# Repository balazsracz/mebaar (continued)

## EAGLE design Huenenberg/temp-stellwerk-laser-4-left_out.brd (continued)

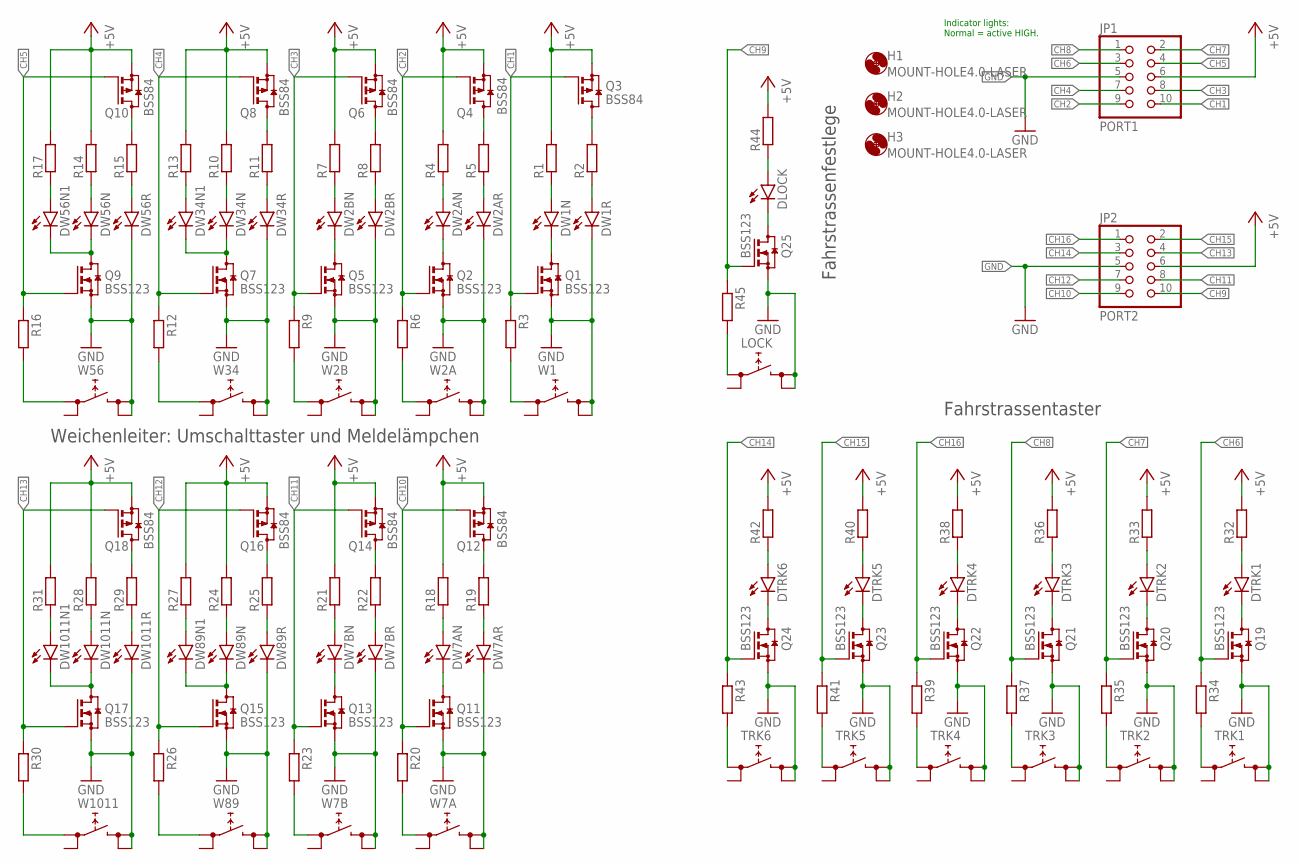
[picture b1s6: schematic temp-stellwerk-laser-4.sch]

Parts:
DLOCK: LEDCHIPLED_0805; CHIPLED_0805
DTRK1, DTRK2, DTRK3, DTRK4, DTRK5, DTRK6: LEDCHIPLED_0805; CHIPLED_0805
DW1N, DW1R, DW2AN, DW2AR, DW7AN, DW7AR: LEDCHIPLED_0603; CHIPLED_0603
DW2BN, DW2BR, DW7BN, DW7BR, DW34N, DW34N1, DW34R, DW56N, DW56N1, DW56R, DW89N, DW89N1, DW89R, DW1011N, DW1011N1, DW1011R: LEDCHIPLED_0805; CHIPLED_0805
H1, H2, H3: MOUNT-HOLE4.0-LASER; MOUNT-HOLE-3.2-4.0-LASER
JP1: PORT1; CON10M
JP2: PORT2; CON10M
LOCK: LOCK; TACTSW-6X6-LASER
Q1, Q2, Q5, Q7, Q9, Q11, Q13, Q15, Q17, Q19, Q20, Q21, Q22, Q23, Q24, Q25: BSS123; SOT23-NCH
Q3, Q4, Q6, Q8, Q10, Q12, Q14, Q16, Q18: BSS84; SOT23
R1, R2, R3, R4, R5, R6, R7, R8, R9, R10, R11, R12, R13, R14, R15, R16, R17, R18, R19, R20, R21, R22, R23, R24, R25, R26, R27, R28, R29, R30, R31, R32, R33, R34, R35, R36, R37, R38, R39, R40, R41, R42, R43, R44, R45: R-EU_R0805; R0805
TRK1, TRK2, TRK3, TRK4, TRK5, TRK6: TACTSW-6X6S; TACTSW-6X6-LASER
W1: W1; TACTSW-6X6-LASER
W2A, W2B, W7A, W7B: TACTSW-6X6S; TACTSW-6X6-LASER
W34, W56, W89, W1011: XOVER; TACTSW-6X6-LASER

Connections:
+5V: JP1.6, JP2.6, Q3.2 (S), Q4.2 (S), Q6.2 (S), Q8.2 (S), Q10.2 (S), Q12.2 (S), Q14.2 (S), Q16.2 (S), Q18.2 (S), R1.2, R4.2, R7.2, R10.2, R13.2, R14.2, R17.2, R18.2, R21.2, R24.2, R27.2, R28.2, R31.2, R32.2, R33.2, R36.2, R38.2, R40.2, R42.2, R44.2
CH1: JP1.10, Q1.1 (G), Q3.1 (G), R3.1
CH2: JP1.9, Q2.1 (G), Q4.1 (G), R6.1
CH3: JP1.8, Q5.1 (G), Q6.1 (G), R9.1
CH4: JP1.7, Q7.1 (G), Q8.1 (G), R12.1
CH5: JP1.4, Q9.1 (G), Q10.1 (G), R16.1
CH6: JP1.3, Q19.1 (G), R34.1
CH7: JP1.2, Q20.1 (G), R35.1
CH8: JP1.1, Q21.1 (G), R37.1
CH9: JP2.10, Q25.1 (G), R45.1
CH10: JP2.9, Q11.1 (G), Q12.1 (G), R20.1
CH11: JP2.8, Q13.1 (G), Q14.1 (G), R23.1
CH12: JP2.7, Q15.1 (G), Q16.1 (G), R26.1
CH13: JP2.4, Q17.1 (G), Q18.1 (G), R30.1
CH14: JP2.3, Q24.1 (G), R43.1
CH15: JP2.2, Q23.1 (G), R41.1
CH16: JP2.1, Q22.1 (G), R39.1
GND: DW1R.C, DW2AR.C, DW2BR.C, DW7AR.C, DW7BR.C, DW34R.C, DW56R.C, DW89R.C, DW1011R.C, JP1.5, JP2.5, LOCK.3 (2.1), LOCK.4 (2.2), Q1.2 (S), Q2.2 (S), Q5.2 (S), Q7.2 (S), Q9.2 (S), Q11.2 (S), Q13.2 (S), Q15.2 (S), Q17.2 (S), Q19.2 (S), Q20.2 (S), Q21.2 (S), Q22.2 (S), Q23.2 (S), Q24.2 (S), Q25.2 (S), TRK1.3 (2.1), TRK1.4 (2.2), TRK2.3 (2.1), TRK2.4 (2.2), TRK3.3 (2.1), TRK3.4 (2.2), TRK4.3 (2.1), TRK4.4 (2.2), TRK5.3 (2.1), TRK5.4 (2.2), TRK6.3 (2.1), TRK6.4 (2.2), W1.3 (2.1), W1.4 (2.2), W2A.3 (2.1), W2A.4 (2.2), W2B.3 (2.1), W2B.4 (2.2), W7A.3 (2.1), W7A.4 (2.2), W7B.3 (2.1), W7B.4 (2.2), W34.3 (2.1), W34.4 (2.2), W56.3 (2.1), W56.4 (2.2), W89.3 (2.1), W89.4 (2.2), W1011.3 (2.1), W1011.4 (2.2)
unnamed: DTRK1.C, Q19.3 (D)
unnamed: DW1N.C, Q1.3 (D)
unnamed: DW1N.A, R1.1
unnamed: DW1R.A, R2.1
unnamed: Q3.3 (D), R2.2
unnamed: DW2AN.C, Q2.3 (D)
unnamed: R3.2, W1.1 (1.1)
unnamed: DW2AN.A, R4.1
unnamed: DW2AR.A, R5.1
unnamed: Q4.3 (D), R5.2
unnamed: R6.2, W2A.1 (1.1)
unnamed: DW2BN.C, Q5.3 (D)
unnamed: DW2BN.A, R7.1
unnamed: DW2BR.A, R8.1
unnamed: Q6.3 (D), R8.2
unnamed: R9.2, W2B.1 (1.1)
unnamed: DW56N.A, R14.1
unnamed: DW34N.A, R10.1
unnamed: DW34R.A, R11.1
unnamed: Q8.3 (D), R11.2
unnamed: R12.2, W34.1 (1.1)
unnamed: DW34N.C, DW34N1.C, Q7.3 (D)
unnamed: DW34N1.A, R13.1
unnamed: DW56R.A, R15.1
unnamed: Q10.3 (D), R15.2
unnamed: R16.2, W56.1 (1.1)
unnamed: DW56N.C, DW56N1.C, Q9.3 (D)
unnamed: DW56N1.A, R17.1
unnamed: DW7AN.C, Q11.3 (D)
unnamed: DW7AN.A, R18.1
unnamed: DW7AR.A, R19.1
unnamed: Q12.3 (D), R19.2
unnamed: R20.2, W7A.1 (1.1)
unnamed: DW7BN.C, Q13.3 (D)
unnamed: DW7BN.A, R21.1
unnamed: DW7BR.A, R22.1
unnamed: Q14.3 (D), R22.2
unnamed: R23.2, W7B.1 (1.1)
unnamed: DW89N.A, R24.1
unnamed: DW89R.A, R25.1
unnamed: Q16.3 (D), R25.2
unnamed: R26.2, W89.1 (1.1)
unnamed: DW89N.C, DW89N1.C, Q15.3 (D)
unnamed: DW89N1.A, R27.1
unnamed: DW1011N.A, R28.1
unnamed: DW1011R.A, R29.1
unnamed: Q18.3 (D), R29.2
unnamed: R30.2, W1011.1 (1.1)
unnamed: DW1011N.C, DW1011N1.C, Q17.3 (D)
unnamed: DW1011N1.A, R31.1
unnamed: DTRK1.A, R32.1
unnamed: DTRK2.C, Q20.3 (D)
unnamed: DTRK2.A, R33.1
unnamed: R34.2, TRK1.1 (1.1)
unnamed: R35.2, TRK2.1 (1.1)
unnamed: DTRK3.C, Q21.3 (D)
unnamed: DTRK3.A, R36.1
unnamed: R37.2, TRK3.1 (1.1)
unnamed: DTRK4.C, Q22.3 (D)
unnamed: DTRK4.A, R38.1
unnamed: R39.2, TRK4.1 (1.1)
unnamed: DTRK5.C, Q23.3 (D)
unnamed: DTRK5.A, R40.1
unnamed: R41.2, TRK5.1 (1.1)
unnamed: DTRK6.C, Q24.3 (D)
unnamed: DTRK6.A, R42.1
unnamed: R43.2, TRK6.1 (1.1)
unnamed: DLOCK.C, Q25.3 (D)
unnamed: DLOCK.A, R44.1
unnamed: LOCK.1 (1.1), R45.2

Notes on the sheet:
Indicator lights: Normal = active HIGH.
Weichenleiter: Umschalttaster und Meldelämpchen
Fahrstrassentaster
Fahrstrassenfestlege

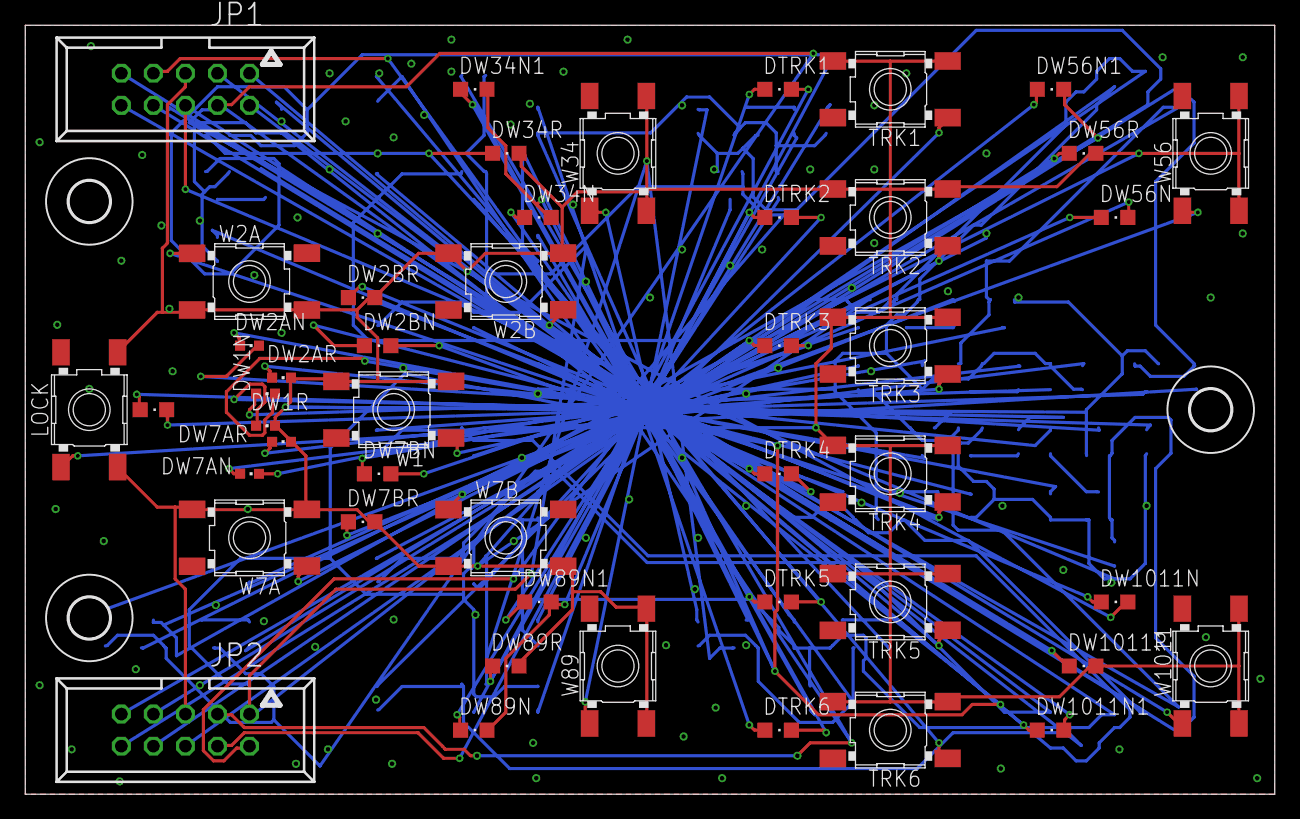
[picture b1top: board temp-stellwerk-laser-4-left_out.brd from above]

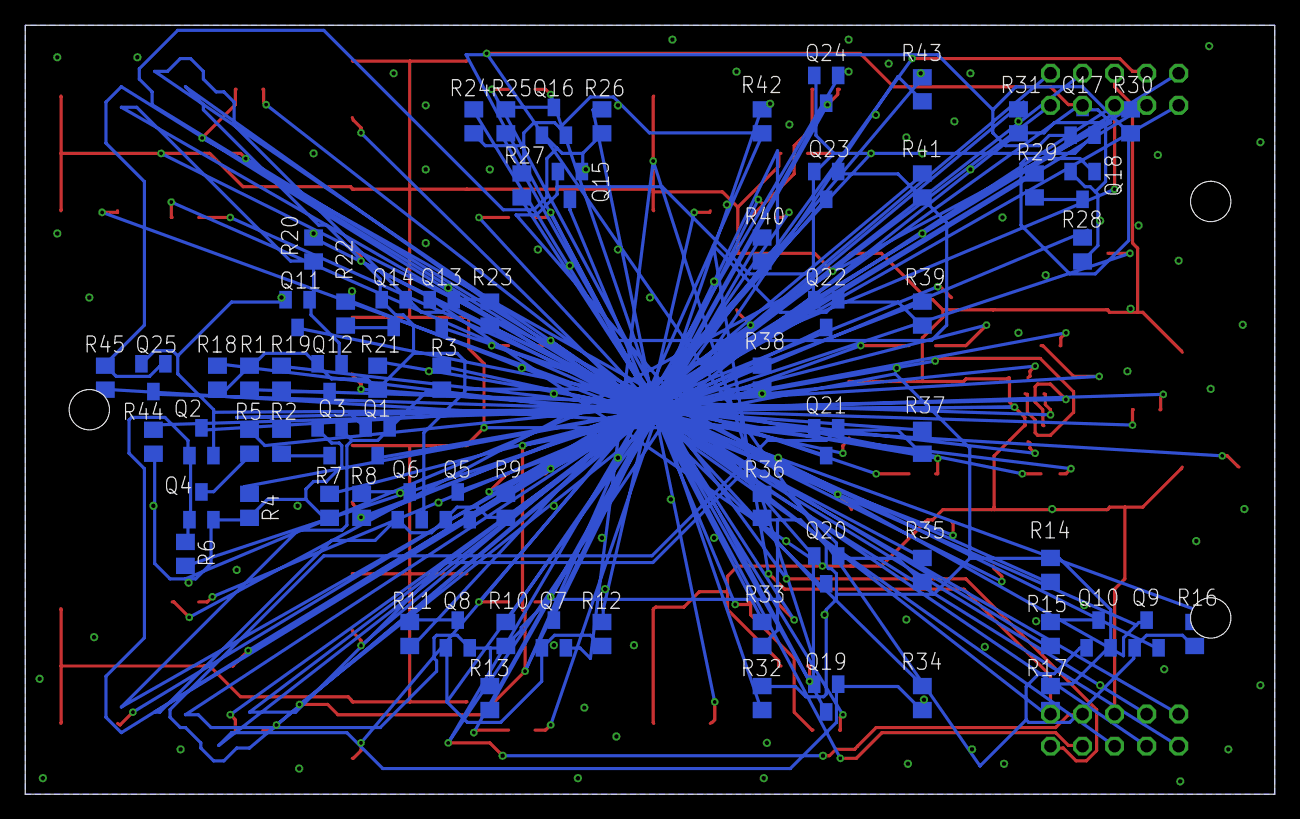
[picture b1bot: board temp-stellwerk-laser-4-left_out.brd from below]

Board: 2 copper layers, 99.1 x 61.0 mm, 138 parts (70 on the bottom side), 88 nets.

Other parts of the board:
PLABEL0: PLABEL0
PLABEL1: PLABEL1
PLABEL2: PLABEL2
PLABEL3: PLABEL3
PLABEL4: PLABEL4
PLABEL5: PLABEL5
PLABEL6: PLABEL6
PLABEL7: PLABEL7
PLABEL8: PLABEL8
PLABEL9: PLABEL9
PLABEL10: PLABEL10
PLABEL11: PLABEL11
PLABEL12: PLABEL12
PLABEL13: PLABEL13
PLABEL14: PLABEL14
PLABEL15: PLABEL15
PLABEL16: PLABEL16
PLABEL17: PLABEL17

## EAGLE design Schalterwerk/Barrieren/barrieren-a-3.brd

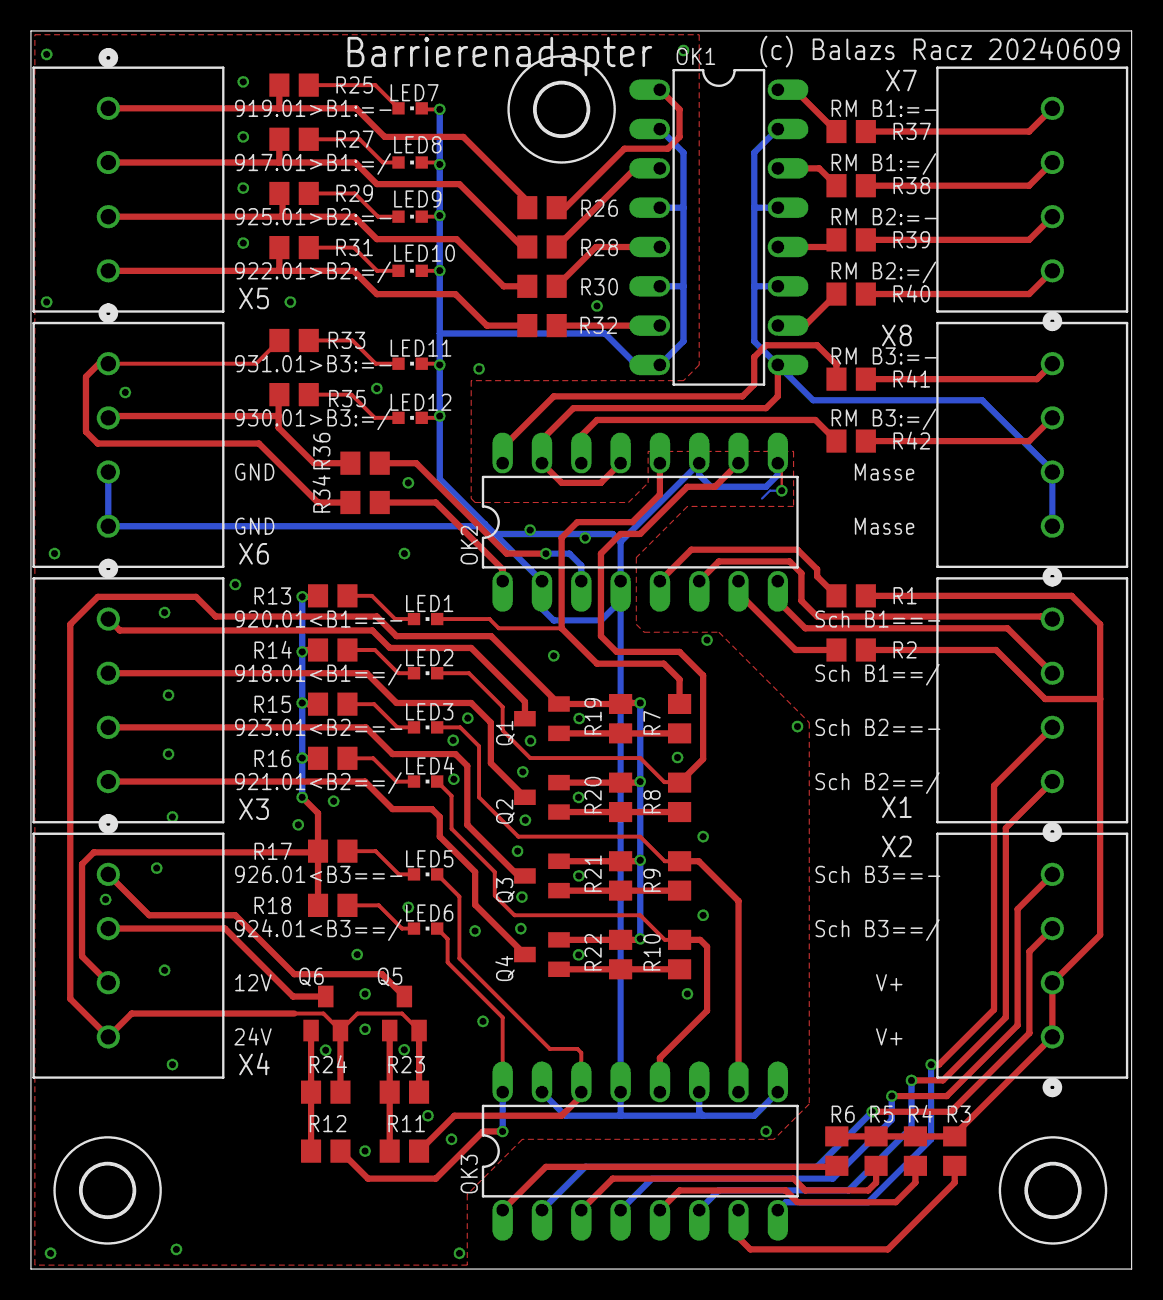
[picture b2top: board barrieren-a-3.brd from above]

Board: 2 copper layers, 71.1 x 80.0 mm, 74 parts (0 on the bottom side), 71 nets.

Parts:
H2, H3, H4: MOUNT-HOLE3.3; 3,3
LED1, LED2, LED3, LED4, LED5, LED6, LED7, LED8, LED9, LED10, LED11, LED12: CHIPLED_0603
OK1, OK2, OK3: PC847; DIL16
Q1, Q2, Q3, Q4, Q5, Q6: BSS84; SOT23-PCH
R1, R2, R3, R4, R5, R6: 1k5; R0805
R7, R8, R9, R10, R11, R12, R19, R20, R21, R22, R23, R24: 100k; R0805
R13, R14, R15, R16, R17, R18: 10k; R0805
R25, R26, R27, R28, R29, R30, R31, R32, R33, R34, R35, R36: 5k; R0805
R37, R38, R39, R40, R41, R42: 100; R0805
X1, X2, X3, X4, X5, X6, X7, X8: PHNX_4P_350CONN_1984989_PXC; PHNX_4P_350

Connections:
+12V: R13.2, R14.2, R15.2, R16.2, R17.2, R18.2, X4.3
+15V: R1.1, R2.1, R3.1, R4.1, R5.1, R6.1, X2.1, X2.2
+24V: Q1.2, Q2.2, Q3.2, Q4.2, Q5.2, Q6.2, R19.2, R20.2, R21.2, R22.2, R23.2, R24.2, X4.4
AGND: OK1.9, OK1.11, OK1.13, OK1.15, OK2.13, OK2.15, X8.1, X8.2
B1-ACT-CL: R25.2, R26.2, X5.1
B1-ACT-CL-RM: R37.1, X7.4
B1-ACT-OP: R27.2, R28.2, X5.2
B1-ACT-OP-RM: R38.1, X7.3
B1-IS-CL: Q1.3, X3.1
B1-IS-CL-SCH: OK2.6, X1.4
B1-IS-OP: Q2.3, X3.2
B1-IS-OP-SCH: OK2.8, X1.3
B2-ACT-CL: R29.2, R30.2, X5.3
B2-ACT-CL-RM: R39.1, X7.2
B2-ACT-OP: R31.2, R32.2, X5.4
B2-ACT-OP-RM: R40.1, X7.1
B2-IS-CL: Q3.3, X3.3
B2-IS-CL-SCH: OK3.8, X1.2
B2-IS-OP: Q4.3, X3.4
B2-IS-OP-SCH: OK3.6, X1.1
B3-ACT-CL: R33.2, R34.2, X6.1
B3-ACT-CL-RM: R41.1, X8.4
B3-ACT-OP: R35.2, R36.2, X6.2
B3-ACT-OP-RM: R42.1, X8.3
B3-IS-CL: Q5.3, X4.1
B3-IS-CL-SCH: OK3.4, X2.4
B3-IS-OP: Q6.3, X4.2
B3-IS-OP-SCH: OK3.2, X2.3
GND: LED7.C, LED8.C, LED9.C, LED10.C, LED11.C, LED12.C, OK1.2, OK1.4, OK1.6, OK1.8, OK2.2, OK2.4, OK2.9, OK2.11, OK3.9, OK3.11, OK3.13, OK3.15, X6.3, X6.4
unnamed: Q1.1, R7.1, R19.1
unnamed: OK2.1, R34.1
unnamed: LED12.A, R35.1
unnamed: LED11.A, R33.1
unnamed: OK2.5, R1.2
unnamed: OK1.12, R39.2
unnamed: OK2.3, R36.1
unnamed: OK2.7, R2.2
unnamed: OK1.10, R40.2
unnamed: OK1.5, R30.1
unnamed: LED1.A, R13.1
unnamed: LED2.A, R14.1
unnamed: LED2.C, OK2.10, R8.2
unnamed: Q2.1, R8.1, R20.1
unnamed: OK3.7, R3.2
unnamed: OK1.7, R32.1
unnamed: LED9.A, R29.1
unnamed: LED3.A, R15.1
unnamed: OK2.16, R41.2
unnamed: LED3.C, OK3.10, R9.2
unnamed: OK2.14, R42.2
unnamed: Q3.1, R9.1, R21.1
unnamed: OK3.5, R4.2
unnamed: LED10.A, R31.1
unnamed: LED4.A, R16.1
unnamed: OK1.16, R37.2
unnamed: LED1.C, OK2.12, R7.2
unnamed: OK1.14, R38.2
unnamed: OK1.1, R26.1
unnamed: LED4.C, OK3.12, R10.2
unnamed: OK1.3, R28.1
unnamed: LED7.A, R25.1
unnamed: LED8.A, R27.1
unnamed: Q4.1, R10.1, R22.1
unnamed: OK3.3, R5.2
unnamed: LED5.A, R17.1
unnamed: LED5.C, OK3.14, R11.2
unnamed: Q5.1, R11.1, R23.1
unnamed: OK3.1, R6.2
unnamed: LED6.A, R18.1
unnamed: LED6.C, OK3.16, R12.2
unnamed: Q6.1, R12.1, R24.1

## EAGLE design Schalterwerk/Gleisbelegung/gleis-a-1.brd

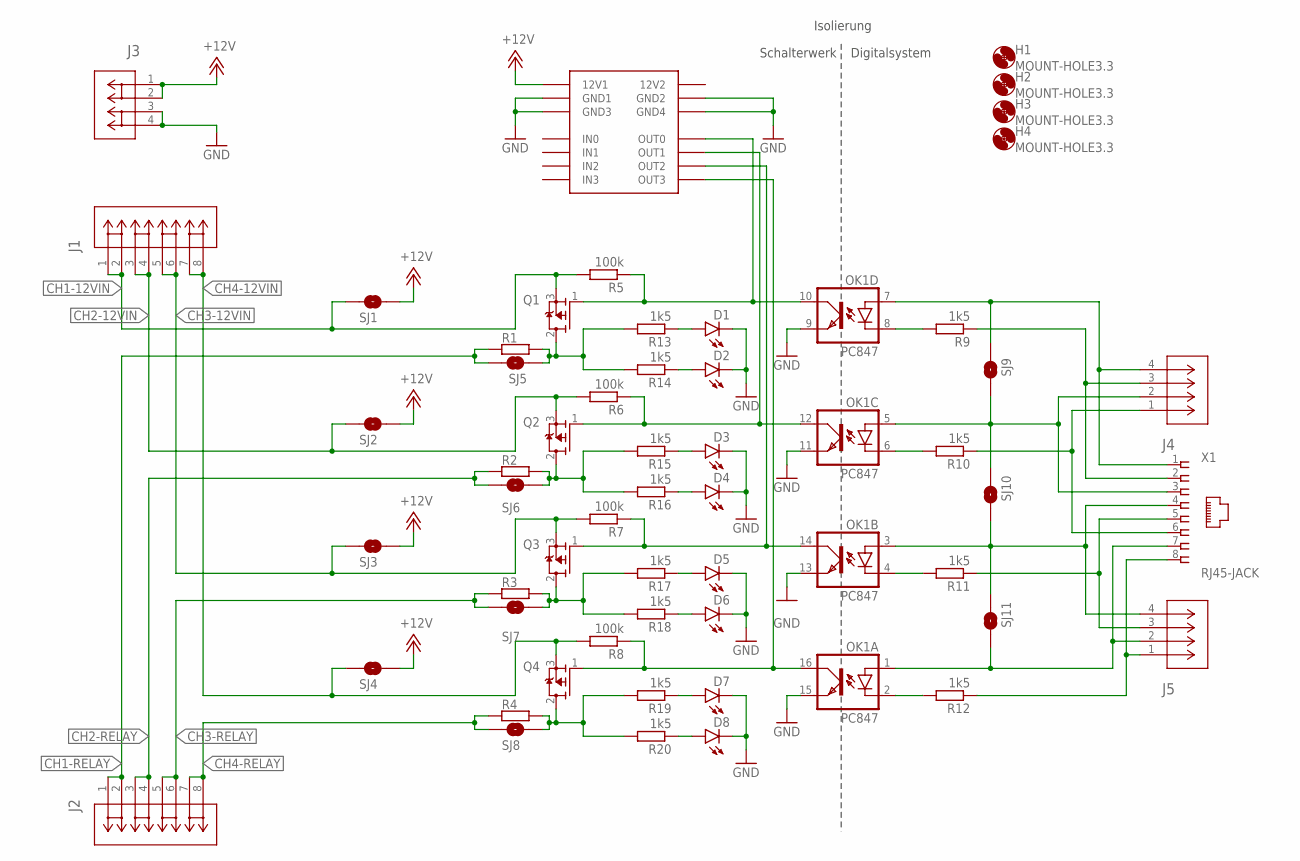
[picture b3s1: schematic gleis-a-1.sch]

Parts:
D1, D3, D5, D7: LEDCHIPLED_0603; CHIPLED_0603
D2, D4, D6, D8: LEDHEADER
H1, H2, H3, H4: MOUNT-HOLE3.3; 3,3
J1, J2: PHNX_4P_508CONN_1017493; PHNX_4P_508
J3: PHNX_2P_508CONN_1017491; PHNX_2P_508
J4, J5: PHNX_4P_350CONN_1984989_PXC; PHNX_4P_350
OK1: PC847; DIL16
Q1, Q2, Q3, Q4: P-MOSFET; DPAK-2
R1, R2, R3, R4: R-EU_VTA52; VTA52
R5, R6, R7, R8: 100k; R0805
R9, R10, R11, R12, R13, R14, R15, R16, R17, R18, R19, R20: 1k5; R0805
SJ1, SJ2, SJ3, SJ4, SJ5, SJ6, SJ7, SJ8, SJ9, SJ10, SJ11: SJRND2; SJ_RND2
X1: RJ45-JACK; RJ45-PULSE-E5J88
X2: IO-HAT; IOBOARD

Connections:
12V2: X2.P$22 (12V2)
+12V: J3.1, J3.2, SJ1.P$2 (2), SJ2.P$2 (2), SJ3.P$2 (2), SJ4.P$2 (2), X2.P$1 (12V1)
CH1-12VIN: J1.1, J1.2, Q1.3 (S), R5.2, SJ1.P$1 (1)
CH1-RELAY: J2.1, J2.2, R1.1, SJ5.P$1 (1)
CH2-12VIN: J1.3, J1.4, Q2.3 (S), R6.2, SJ2.P$1 (1)
CH2-RELAY: J2.3, J2.4, R2.1, SJ6.P$1 (1)
CH3-12VIN: J1.5, J1.6, Q3.3 (S), R7.2, SJ3.P$1 (1)
CH3-RELAY: J2.5, J2.6, R3.1, SJ7.P$1 (1)
CH4-12VIN: J1.7, J1.8, Q4.3 (S), R8.2, SJ4.P$1 (1)
CH4-RELAY: J2.7, J2.8, R4.1, SJ8.P$1 (1)
GND: D1.C, D2.C, D3.C, D4.C, D5.C, D6.C, D7.C, D8.C, J3.3, J3.4, OK1.9 (EMIT), OK1.11 (EMIT), OK1.13 (EMIT), OK1.15 (EMIT), X2.P$2 (GND1), X2.P$11 (GND3), X2.P$12 (GND4), X2.P$21 (GND2)
unnamed: Q1.2 (D), R1.2, R13.2, R14.2, SJ5.P$2 (2)
unnamed: OK1.12 (COL), Q2.1 (G), R6.1, X2.P$19 (OUT1)
unnamed: J4.4, OK1.7 (A), SJ9.P$2 (2), X1.1
unnamed: J4.3, R9.1, X1.2
unnamed: OK1.14 (COL), Q3.1 (G), R7.1, X2.P$18 (OUT2)
unnamed: J4.2, OK1.5 (A), SJ9.P$1 (1), SJ10.P$2 (2), X1.3
unnamed: OK1.4 (C), R11.2
unnamed: D1.A, R13.1
unnamed: OK1.10 (COL), Q1.1 (G), R5.1, X2.P$20 (OUT0)
unnamed: Q2.2 (D), R2.2, R15.2, R16.2, SJ6.P$2 (2)
unnamed: Q3.2 (D), R3.2, R17.2, R18.2, SJ7.P$2 (2)
unnamed: OK1.16 (COL), Q4.1 (G), R8.1, X2.P$17 (OUT3)
unnamed: Q4.2 (D), R4.2, R19.2, R20.2, SJ8.P$2 (2)
unnamed: J5.3, R11.1, X1.5
unnamed: J5.2, OK1.1 (A), SJ11.P$1 (1), X1.7
unnamed: J5.1, R12.1, X1.8
unnamed: OK1.8 (C), R9.2
unnamed: OK1.6 (C), R10.2
unnamed: OK1.2 (C), R12.2
unnamed: J4.1, R10.1, X1.6
unnamed: D2.A, R14.1
unnamed: D3.A, R15.1
unnamed: D4.A, R16.1
unnamed: D5.A, R17.1
unnamed: J5.4, OK1.3 (A), SJ10.P$1 (1), SJ11.P$2 (2), X1.4
unnamed: D6.A, R18.1
unnamed: D7.A, R19.1
unnamed: D8.A, R20.1

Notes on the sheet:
Isolierung
Schalterwerk
Digitalsystem

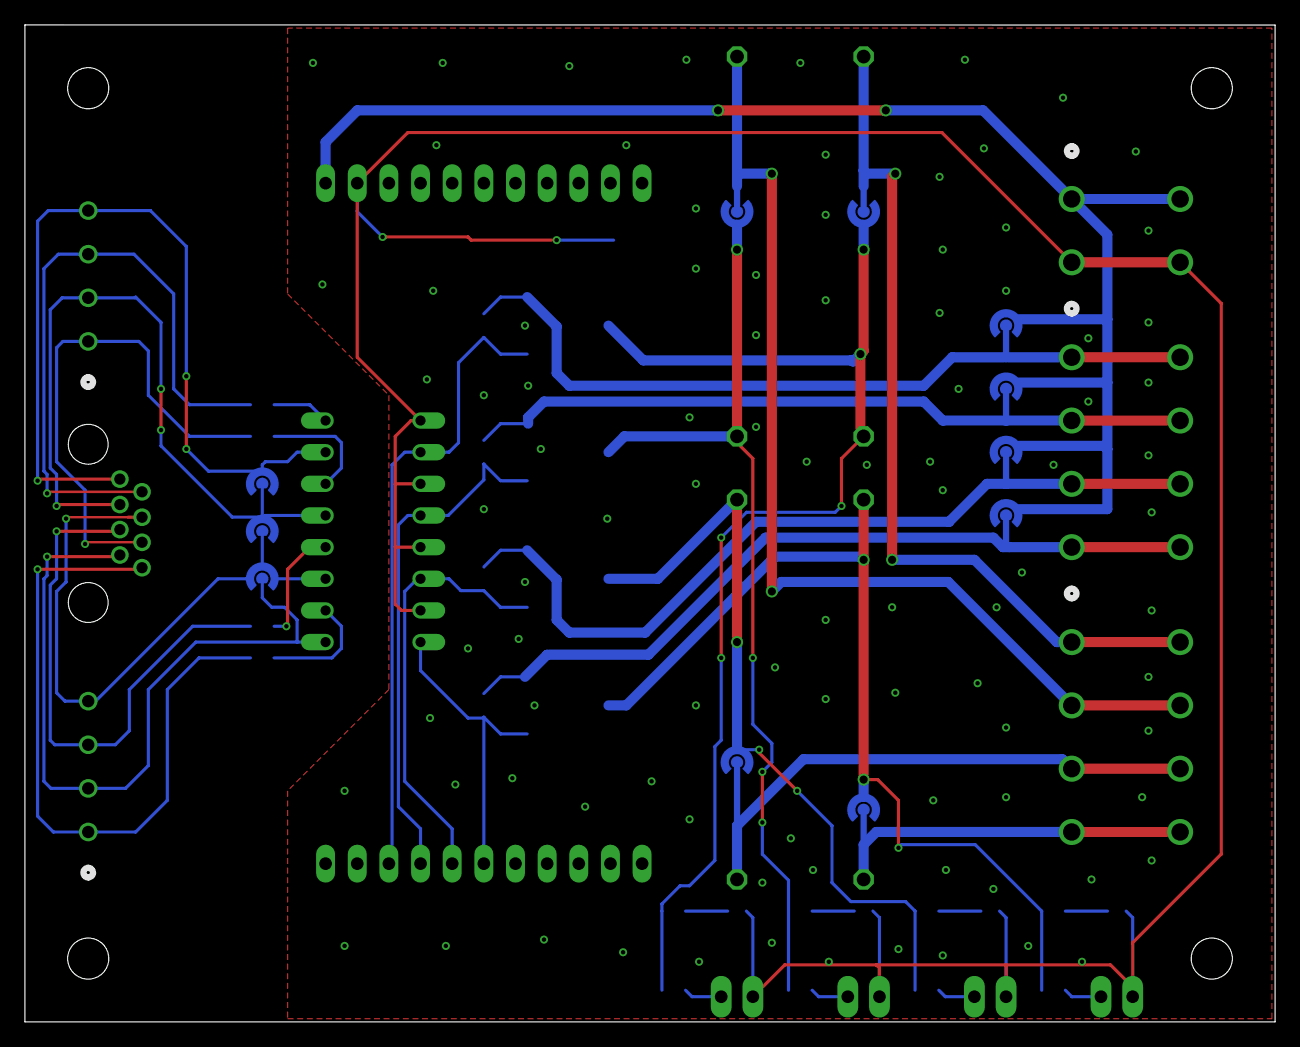
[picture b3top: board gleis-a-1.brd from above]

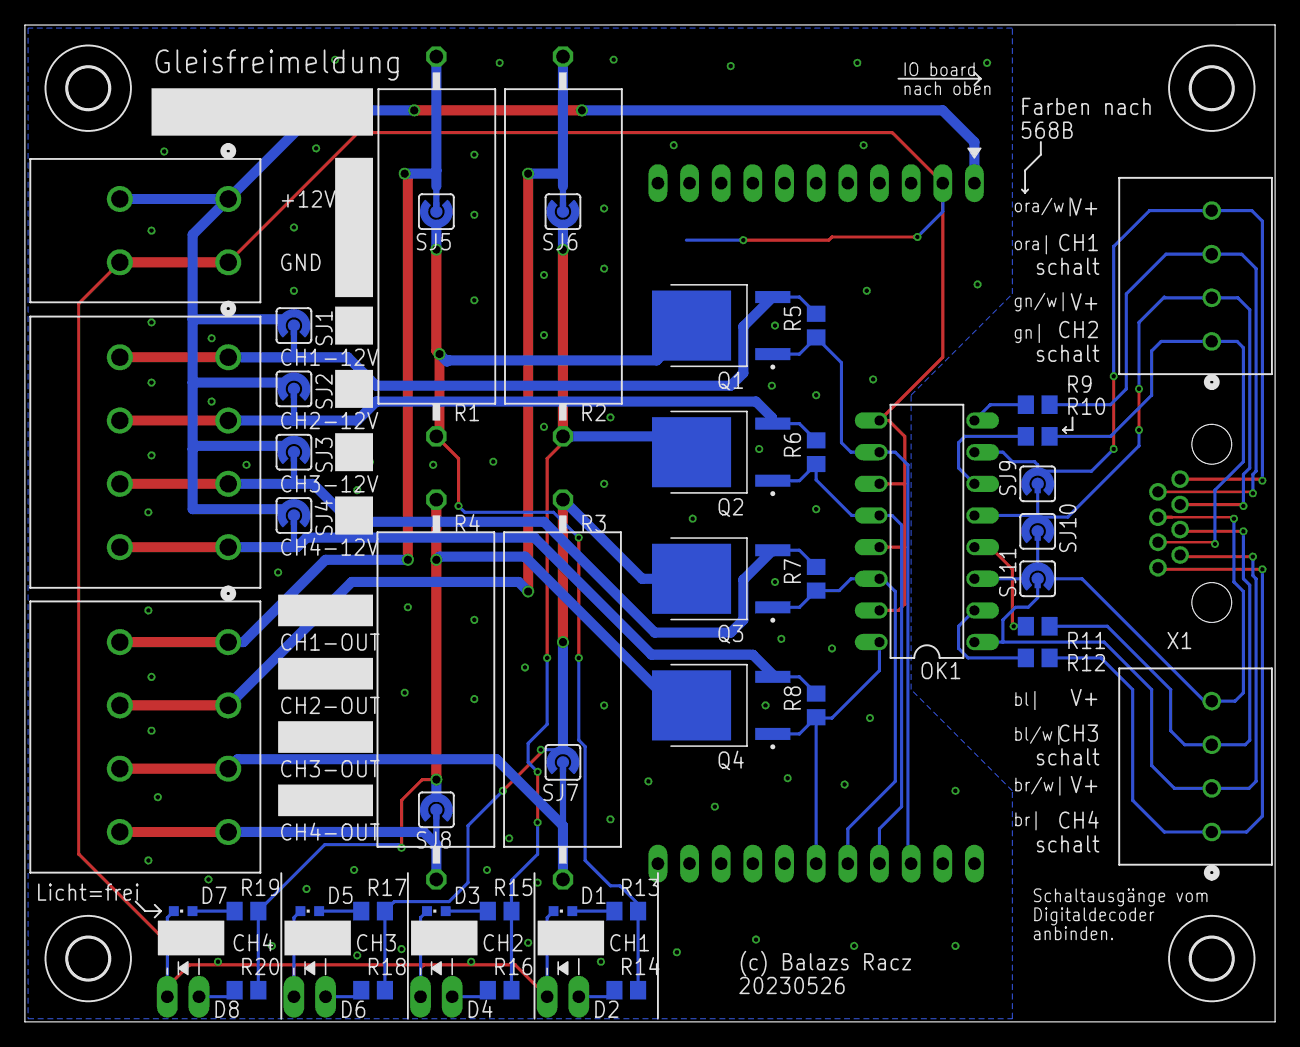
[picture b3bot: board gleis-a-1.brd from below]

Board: 2 copper layers, 100.3 x 80.0 mm, 55 parts (55 on the bottom side), 38 nets.

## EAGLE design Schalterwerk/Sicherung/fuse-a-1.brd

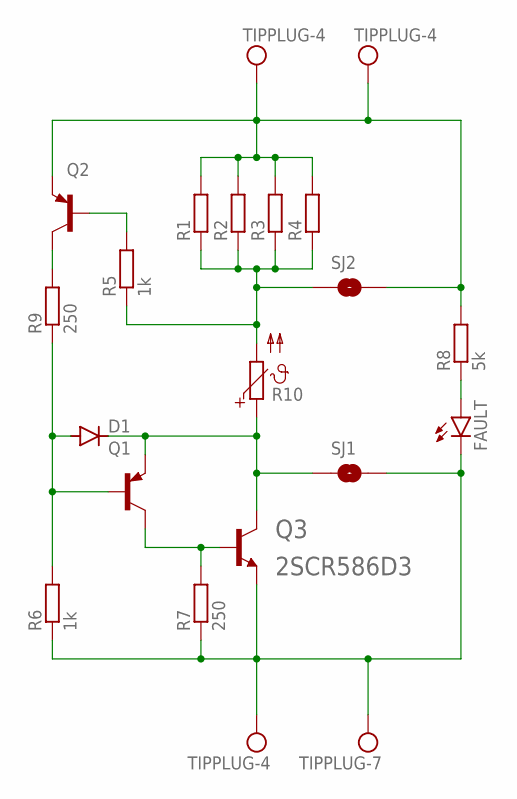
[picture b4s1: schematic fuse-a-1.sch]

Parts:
D1: DIODE-MINIMELF; MINIMELF
FAULT: LEDCHIPLED_0603; CHIPLED_0603
Q1, Q2: BCX71SMD; SOT23
Q3: 2SCR586D3; D-PAK_TO252AA
R1, R2, R3, R4: R-EU_R2512; R2512
R5, R6: 1k; R0805
R7, R9: 250; R0805
R8: 5k; R0805
R10: PTC_1812; PTC1812
SJ1, SJ2: SJRND2; SJ_RND2
U$1, U$2, U$4: TIPPLUG-4; BANANAPLUG-4-LUG
U$3: TIPPLUG-7; BANANAPLUG-7-LUG

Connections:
FUSEIN: R1.1, R2.1, R3.1, R4.1, R5.1, R10.2, SJ2.P$1 (1)
FUSEOUT: D1.C, Q1.2 (E), Q3.4 (C), R10.1, SJ1.P$1 (1)
unnamed: Q2.1 (B), R5.2
unnamed: D1.A, Q1.1 (B), R6.2, R9.1
unnamed: Q1.3 (C), Q3.1 (B), R7.2
unnamed: FAULT.A, R8.1
unnamed: Q2.3 (C), R9.2
VIN: Q2.2 (E), R1.2, R2.2, R3.2, R4.2, R8.2, SJ2.P$2 (2), U$1.4MM, U$4.4MM
VOUT: FAULT.C, Q3.3 (E), R6.1, R7.1, SJ1.P$2 (2), U$2.4MM, U$3.7MM

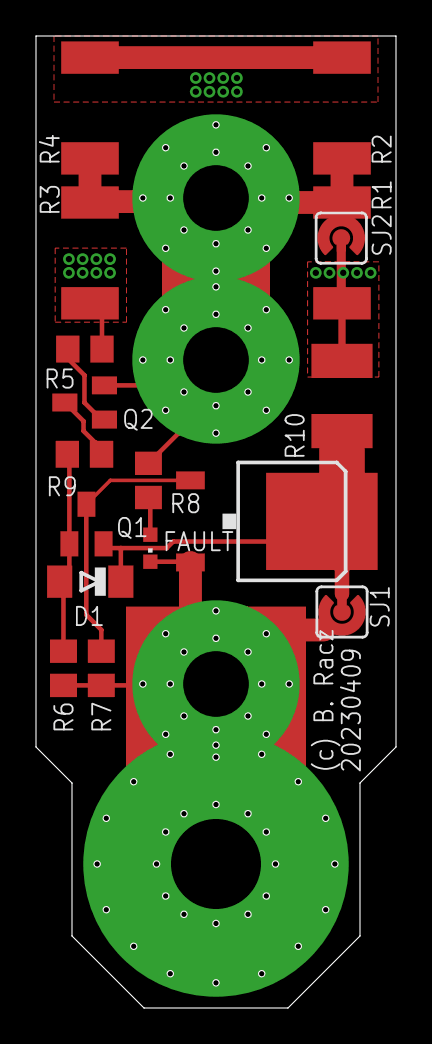
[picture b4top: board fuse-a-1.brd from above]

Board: 2 copper layers, 20.0 x 54.0 mm, 21 parts (0 on the bottom side), 9 nets.
